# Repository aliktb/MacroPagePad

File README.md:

# MacroPagePad
<b>A simple Arduino based HID keypad with up to 60 individual button functions and a rotary encoder </b>

## About

This keypad allows up to 60 individual button-based functions. The MPP has 4 'pages'. The current page is represented by the LED that is lit at the top. Pressing the bottom right page allows you to move to the next page. Each page can allocate a different function for a button. For example, button number 1 at the top left may have the function to stop media playback. Switching to page 2, the same button can be used to take a screenshot etc. This can be really useful when using a program such as photoshop to have specific keyboard shortcuts mapped to buttons on one page and a different set of shortcuts can be mapped for Kicad on a second page. Each page has 15 available buttons to program meaning up to 60 separate functions! The rotary encoder can also be used the same way by changing its behaviour depending on the page.  

## Hardware

The <i>HID_KEYPAD</i> folder contains all the neccesary files to view the PCB schematic and layout within Kicad as well as gerber files. 

This project is based on the Arduino Pro Micro. Modifications will need to be made to the PCB to accomodate the wider Arduino Pro Mini. By using female header pins, you can replace the Arduino Pro micro by just lifting it out of the socket. This PCB uses all THT components. Note, the mounting holes are plated and connected to ground. Be careful not to short any pins on the back of the PCB by resting it on a metal surface while powered on. The soldered PCB should look like this. For reference, this is using Gateron green switches:

The switches are based on the Cherry MX profile and are compitible with a variety of switches such as Gateron. The switches are arranged in a 4x4 matrix config similar to membrane switch matrices. Footprints are included for other brands in the <i>keyswitches.pretty-master</i> folder if you want to replace the footprints.
 
## Software

Use <i>MacroPagePad.ino</i> with the neccesary libraries installed in the arduino IDE. The <i>readKp4x4()</i> is used to determine the button functions. Aside from media controls and keyboard shortcuts, the buttons can't do much on their own. However, using a program such as [AutoHotKey](https://www.autohotkey.com/) makes the MacroPagePad very useful for Windows. This allows you to open and close apps, autofill forms, controlling mouse movements and much more. Simply create a script that is triggered by a random shortcut that isn't used by any other program and create the same shortcut in the .ino file. A good set of shortcuts are simply F13-F24 keys. The keys exist in Windows, Mac and Linux but aren't found on most keyboards. Because of this, these keys aren't really used as shortcuts in a lot of programs so can be used with AutoHotKey or similar. Linux also has tools to set up custom shortcuts. [Hammerspoon](http://www.hammerspoon.org/) is a tool available for MacOS with similar functionality of AHK. 

The rotary controller is setup to control the system volume but can be remapped to zoom, scroll, increase brightness etc. This can also be done with multiple pages. The encoder also has a push button currently mapped to mute/unmute. 

## Troubleshooting/Issues

Be sure to flag any issues or feature requests through Github. This project is open to contribution via pull requests.  

## Credits

The following libraries have been used to make this project possible:

https://github.com/Chris--A/Keypad

https://github.com/BennehBoy/clickEncoder

https://github.com/PaulStoffregen/TimerOne

https://github.com/NicoHood/HID

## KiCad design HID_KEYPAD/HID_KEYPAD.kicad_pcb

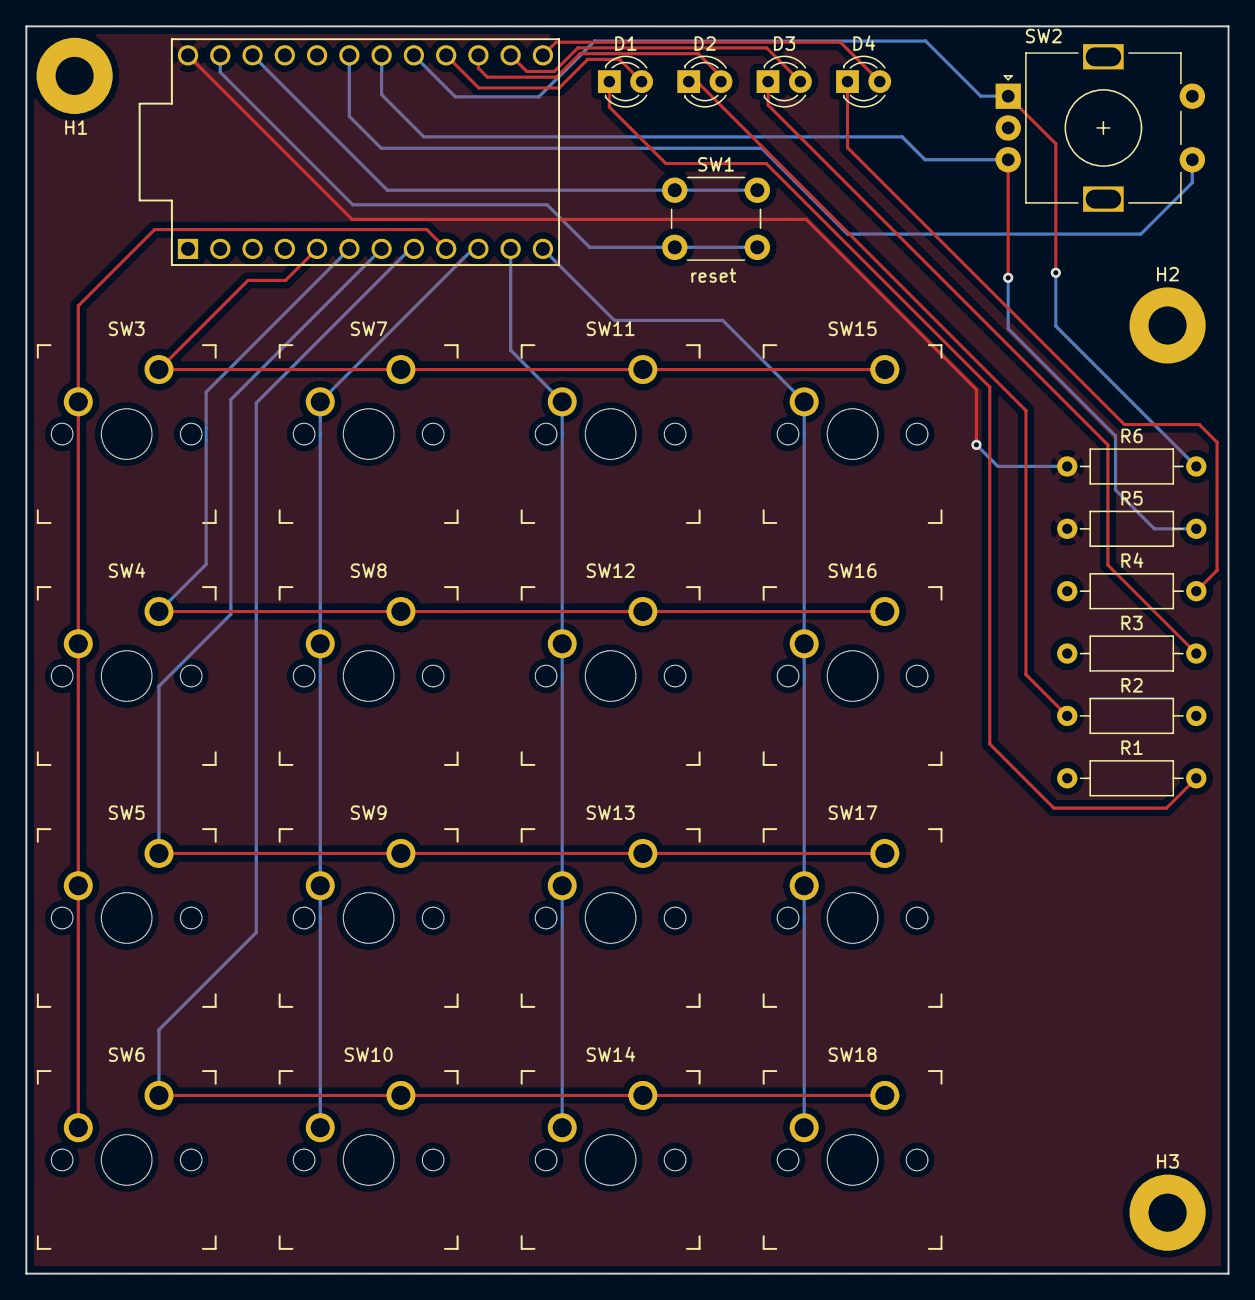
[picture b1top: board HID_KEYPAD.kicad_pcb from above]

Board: 2 copper layers, 94.7 x 98.2 mm, 32 parts (0 on the bottom side), 23 nets.

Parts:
D1, D2, D3, D4: LED; LED_D3.0mm
H1, H2, H3: MountingHole_Pad; MountingHole_3mm_Pad
R1, R2, R3, R4: R; R_Axial_DIN0207_L6.3mm_D2.5mm_P10.16mm_Horizontal
R5, R6: 10k; R_Axial_DIN0207_L6.3mm_D2.5mm_P10.16mm_Horizontal
SW1: reset; SW_PUSH_6mm
SW2: Rotary_Encoder_Switch; RotaryEncoder_Alps_EC11E-Switch_Vertical_H20mm
SW3, SW4, SW5, SW6, SW7, SW8, SW9, SW10, SW11, SW12, SW13, SW14, SW15, SW16, SW17, SW18: SW_Push; SW_MX
U1: ProMicro

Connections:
+5V: R5.1, R6.1, U1.24
/matrix/C1: SW3.2, SW4.2, SW5.2, SW6.2, U1.9
/matrix/C2: SW7.2, SW8.2, SW9.2, SW10.2, U1.10
/matrix/C3: SW11.2, SW12.2, SW13.2, SW14.2, U1.11
/matrix/C4: SW15.2, SW16.2, SW17.2, SW18.2, U1.12
/matrix/R1: SW3.1, SW7.1, SW11.1, SW15.1, U1.5
/matrix/R2: SW4.1, SW8.1, SW12.1, SW16.1, U1.6
/matrix/R3: SW5.1, SW9.1, SW13.1, SW17.1, U1.7
/matrix/R4: SW6.1, SW10.1, SW14.1, SW18.1, U1.8
CLK: R6.2, SW2.A, U1.17
DT: R5.2, SW2.B, U1.18
GND: H1.1, H2.1, H3.1, R1.1, R2.2, R3.1, R4.1, SW2.C, SW2.S2, U1.3
unnamed: D1.1, R1.2
unnamed: D1.2, U1.16
unnamed: D2.1, R2.1
unnamed: D2.2, U1.15
unnamed: D3.1, R3.2
unnamed: D3.2, U1.14
unnamed: D4.1, R4.2
unnamed: D4.2, U1.13
unnamed: SW1.1, U1.22
unnamed: SW1.2, U1.23
SW: SW2.S1, U1.19
